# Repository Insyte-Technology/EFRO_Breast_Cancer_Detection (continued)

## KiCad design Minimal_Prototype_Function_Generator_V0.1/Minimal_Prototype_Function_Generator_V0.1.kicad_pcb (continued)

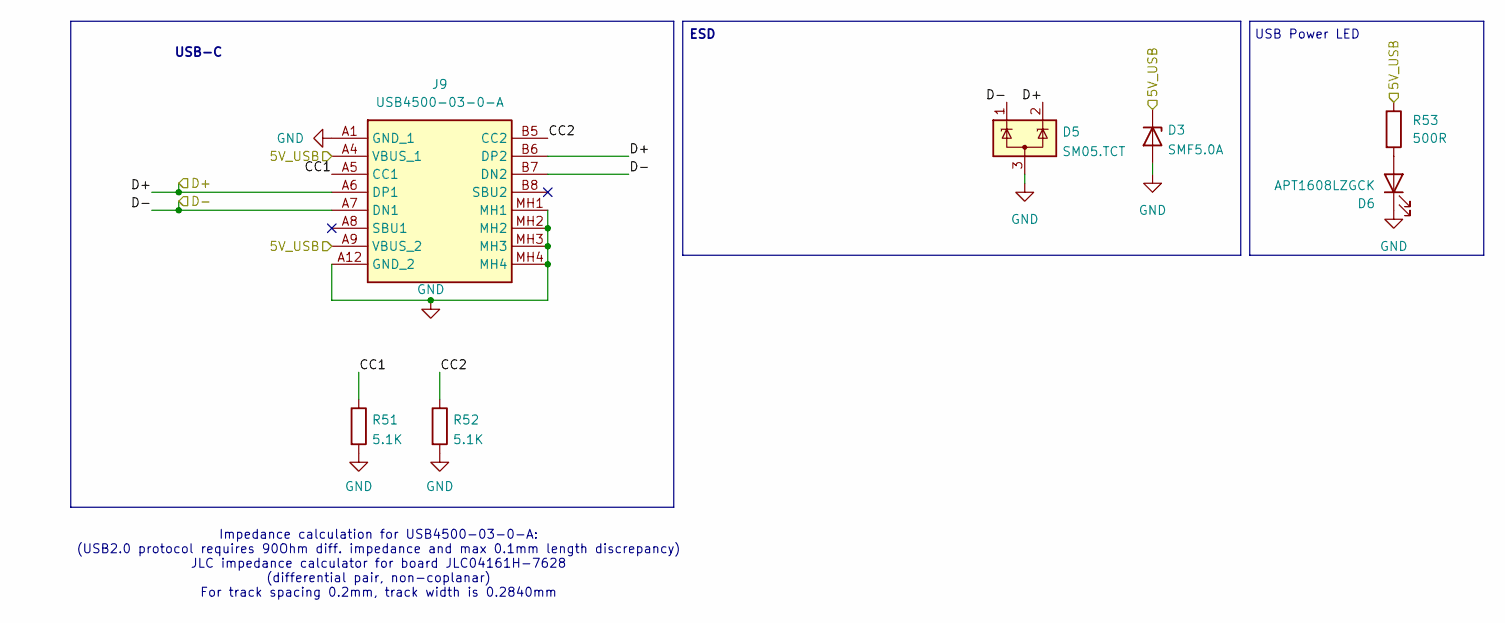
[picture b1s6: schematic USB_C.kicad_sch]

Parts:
D3: SMF5.0A; SODFL3618X110N; Manufacturer_Part_Number SMF5.0A; LCSC Part # C193402
D5: SM05.TCT; SOT95P237X125-3N; Manufacturer_Part_Number SM05.TCT; LCSC Part # C2687125
D6: APT1608LZGCK; CSL1901MW1; Manufacturer_Part_Number APT1608LZGCK
J9: USB4500-03-0-A; USB4500030A; Mouser Part Number 640-USB4500030A
R51, R52: 5.1K; R_0603; Manufacturer_Part_Number RT0603FRD075K1L; LCSC Part # C23186
R53: 500R; R_0603; Manufacturer_Part_Number RC0603FR-1325K5L

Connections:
/Power/5V: D3.1 (K), J9.A4 (VBUS_1), J9.A9 (VBUS_2), R53.1; also elsewhere on the board
/USB_C/CC1: J9.A5 (CC1), R51.1
/USB_C/CC2: J9.B5 (CC2), R52.1
/USB_C/D+: D5.2 (K), J9.A6 (DP1), J9.B6 (DP2); also elsewhere on the board
/USB_C/D-: D5.1 (K), J9.A7 (DN1), J9.B7 (DN2); also elsewhere on the board
GND: D3.2 (A), D5.3 (A), D6.1 (K), J9.A1 (GND_1), J9.A12 (GND_2), J9.MH1, J9.MH2, J9.MH3, J9.MH4, R51.2, R52.2; also elsewhere on the board
unnamed: D6.2 (A), R53.2

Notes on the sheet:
Impedance calculation for USB4500-03-0-A: (USB2.0 protocol requires 90Ohm diff. impedance and max 0.1mm length discrepancy) JLC impedance calculator for board JLC04161H-7628 (differential pair, non-coplanar) For track spacing 0.2mm, track width is 0.2840mm
ESD
USB-C
USB Power LED

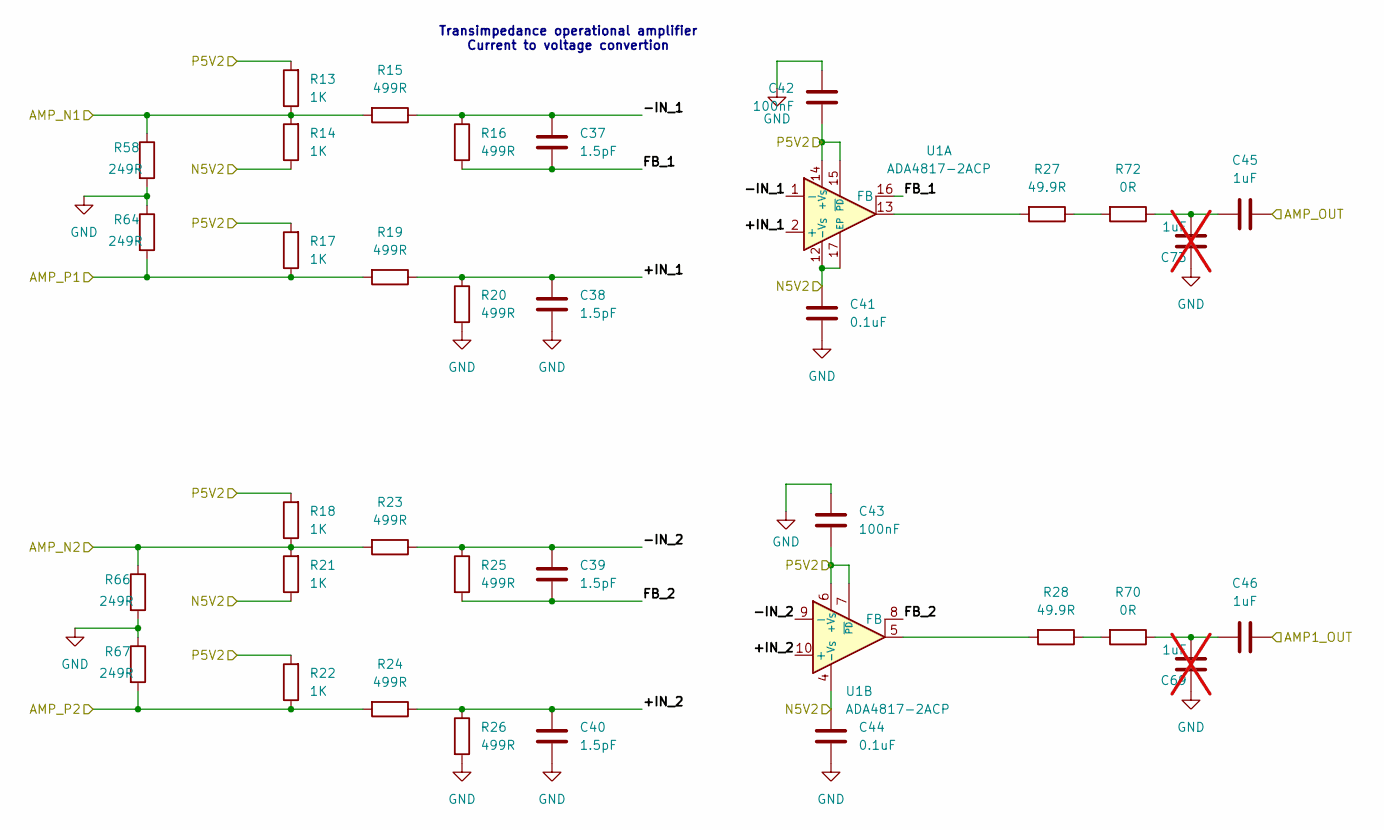
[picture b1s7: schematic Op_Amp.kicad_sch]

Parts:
C37, C38, C39, C40: 1.5pF; C_0603
C41, C44: 0.1uF; C_0603
C42, C43: 100nF; C_0603
C45, C46: 1uF; C_0603
C69, C73: 1uF; C_0603; not fitted
R13, R14, R17, R18, R21, R22: 1K; R_0603
R15, R16, R19, R20, R23, R24, R25, R26: 499R; R_0603
R27, R28: 49.9R; R_0603
R58, R64, R66, R67: 249R; R_0603
R70, R72: 0R; R_0603
U1: ADA4817-2ACP; Analog_LFCSP-16-1EP_4x4mm_P0.65mm_EP2.35x2.35mm

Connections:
/Function Generator/I_Out_N1: R13.1, R14.2, R15.2, R58.1; also elsewhere on the board
/Function Generator/I_Out_N2: R18.1, R21.2, R23.2, R66.1; also elsewhere on the board
/Function Generator/I_Out_P1: R17.1, R19.2, R64.2; also elsewhere on the board
/Function Generator/I_Out_P2: R22.1, R24.2, R67.2; also elsewhere on the board
/Output_Stage/N5V2: C41.1, C44.1, R14.1, R21.1, U1.4 (-V_{S}), U1.12 (-V_{S}), U1.17 (EP); also elsewhere on the board
/Output_Stage/Op_Amp_1/+IN_1: C38.1, R19.1, R20.1, U1.2 (+)
/Output_Stage/Op_Amp_1/+IN_2: C40.1, R24.1, R26.1, U1.10 (+)
/Output_Stage/Op_Amp_1/-IN_1: C37.1, R15.1, R16.1, U1.1 (-)
/Output_Stage/Op_Amp_1/-IN_2: C39.1, R23.1, R25.1, U1.9 (-)
/Output_Stage/Op_Amp_1/AMP1_OUT: C46.2; also elsewhere on the board
/Output_Stage/Op_Amp_1/AMP_OUT: C45.2; also elsewhere on the board
/Output_Stage/Op_Amp_1/FB_1: C37.2, R16.2, U1.16 (FB)
/Output_Stage/Op_Amp_1/FB_2: C39.2, R25.2, U1.8 (FB)
/Output_Stage/P5V2: C42.2, C43.2, R13.2, R17.2, R18.2, R22.2, U1.6 (+V_{S}), U1.7 (~PD), U1.14 (+V_{S}), U1.15 (~PD); also elsewhere on the board
GND: C38.2, C40.2, C41.2, C42.1, C43.1, C44.2, C69.2, C73.2, R20.2, R26.2, R58.2, R64.1, R66.2, R67.1; also elsewhere on the board
unnamed: C45.1, C73.1, R72.1
unnamed: C46.1, C69.1, R70.1
unnamed: R27.1, R72.2
unnamed: R27.2, U1.13
unnamed: R28.1, R70.2
unnamed: R28.2, U1.5

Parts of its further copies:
C47, C48, C49, C50: 1.5pF; C_0603
C51, C53: 100nF; C_0603
C52, C54: 0.1uF; C_0603
C55, C56: 1uF; C_0603
C72, C74: 1uF; C_0603; not fitted
R29, R30, R31, R32, R33, R34: 1K; R_0603
R35, R36, R37, R38, R39, R40, R41, R42: 499R; R_0603
R43, R44: 49.9R; R_0603
R63, R65, R68, R69: 249R; R_0603
R71, R73: 0R; R_0603
U3: ADA4817-2ACP; Analog_LFCSP-16-1EP_4x4mm_P0.65mm_EP2.35x2.35mm

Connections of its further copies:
/Function Generator/I_Out_N3: R29.1, R30.2, R35.2, R63.1; also elsewhere on the board
/Function Generator/I_Out_N4: R32.1, R33.2, R37.2, R68.1; also elsewhere on the board
/Function Generator/I_Out_P3: R31.1, R36.2, R65.2; also elsewhere on the board
/Function Generator/I_Out_P4: R34.1, R38.2, R69.2; also elsewhere on the board
/Output_Stage/N5V2: C52.1, C54.1, R30.1, R33.1, U3.4 (-V_{S}), U3.12 (-V_{S}), U3.17 (EP); also elsewhere on the board
/Output_Stage/Op_Amp_2/+IN_1: C48.1, R36.1, R40.1, U3.2 (+)
/Output_Stage/Op_Amp_2/+IN_2: C50.1, R38.1, R42.1, U3.10 (+)
/Output_Stage/Op_Amp_2/-IN_1: C47.1, R35.1, R39.1, U3.1 (-)
/Output_Stage/Op_Amp_2/-IN_2: C49.1, R37.1, R41.1, U3.9 (-)
/Output_Stage/Op_Amp_2/AMP1_OUT: C56.2; also elsewhere on the board
/Output_Stage/Op_Amp_2/AMP_OUT: C55.2; also elsewhere on the board
/Output_Stage/Op_Amp_2/FB_1: C47.2, R39.2, U3.16 (FB)
/Output_Stage/Op_Amp_2/FB_2: C49.2, R41.2, U3.8 (FB)
/Output_Stage/P5V2: C51.2, C53.2, R29.2, R31.2, R32.2, R34.2, U3.6 (+V_{S}), U3.7 (~PD), U3.14 (+V_{S}), U3.15 (~PD); also elsewhere on the board
GND: C48.2, C50.2, C51.1, C52.2, C53.1, C54.2, C72.2, C74.2, R40.2, R42.2, R63.2, R65.1, R68.2, R69.1; also elsewhere on the board
unnamed: C55.1, C74.1, R73.1
unnamed: C56.1, C72.1, R71.1
unnamed: R43.1, R73.2
unnamed: R43.2, U3.13
unnamed: R44.1, R71.2
unnamed: R44.2, U3.5

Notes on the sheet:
Transimpedance operational amplifier Current to voltage convertion

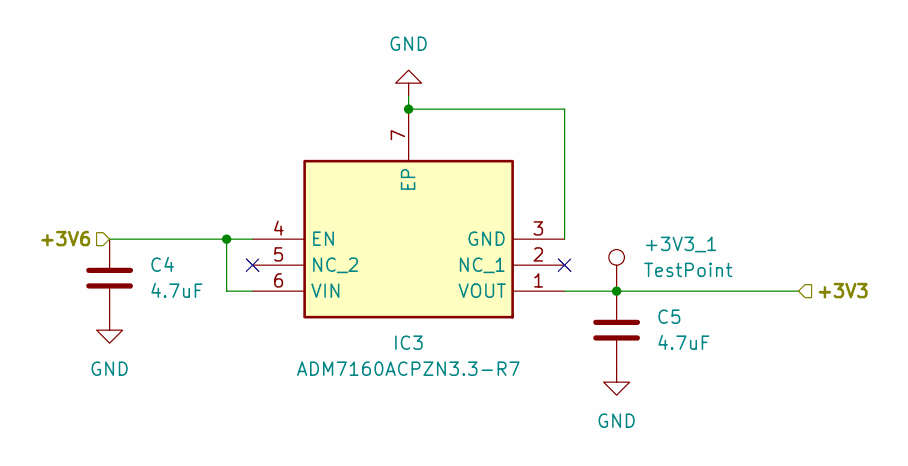
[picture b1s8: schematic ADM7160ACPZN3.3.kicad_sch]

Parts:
+3V3_1: TestPoint; Testpoint_hole
C4, C5: 4.7uF; C_0603
IC3: ADM7160ACPZN3.3-R7; SON65P200X200X65-7N-D; Mouser Part Number 584-DM7160ACPZN3.3R7

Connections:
/Power/ADM7160ACPZN3.3_1/+3V3: +3V3_1.1 (1_1), C5.1, IC3.1 (VOUT); also elsewhere on the board
/Power/ADM7160ACPZN3.3_1/+3V6: C4.1, IC3.4 (EN), IC3.6 (VIN); also elsewhere on the board
GND: C4.2, C5.2, IC3.3 (GND), IC3.7 (EP); also elsewhere on the board

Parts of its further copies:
+3V3_3, +3V3_4, +3V3_5: TestPoint; Testpoint_hole
C33, C34, C35, C36, C67, C68: 4.7uF; C_0603
IC6, IC7, IC8: ADM7160ACPZN3.3-R7; SON65P200X200X65-7N-D; Mouser Part Number 584-DM7160ACPZN3.3R7

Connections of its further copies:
/Function Generator/AVDD: +3V3_3.1 (1_1), C34.1, IC6.1 (VOUT); also elsewhere on the board
/Function Generator/CVDDX: +3V3_4.1 (1_1), C36.1, IC7.1 (VOUT); also elsewhere on the board
/Power/ADM7160ACPZN3.3_1/+3V6: C33.1, C35.1, C67.1, IC6.4 (EN), IC6.6 (VIN), IC7.4 (EN), IC7.6 (VIN), IC8.4 (EN), IC8.6 (VIN); also elsewhere on the board
/Power/VDD_STM32: +3V3_5.1 (1_1), C68.1, IC8.1 (VOUT); also elsewhere on the board
GND: C33.2, C34.2, C35.2, C36.2, C67.2, C68.2, IC6.3 (GND), IC6.7 (EP), IC7.3 (GND), IC7.7 (EP), IC8.3 (GND), IC8.7 (EP); also elsewhere on the board

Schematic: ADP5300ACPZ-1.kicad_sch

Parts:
+3V6_1, +5V_1: TestPoint; Testpoint_hole
C2, C3: 10uF; C_0603
D1: LED GREEN; CSL1901MW1
IC2: ADP5300ACPZ-1-R7; SON50P300X300X85-11N-D; Mouser Part Number 584-ADP5300ACPZ-1-R7
L1: MLP2016V2R2MT0S1; INDC2016X100N; Mouser Part Number 810-MLP2016H2R2MT0S1
R1: 499K; R_0603
R2: 5K; R_0603
R3: 0R; R_0603

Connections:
/Power/5V: +5V_1.1 (1_1), C2.1, IC2.1 (EN), IC2.3 (SYNC/MODE), IC2.10 (PVIN); also elsewhere on the board
/Power/ADM7160ACPZN3.3_1/+3V6: +3V6_1.1 (1_1), C3.1, IC2.5 (FB), L1.2, R2.1; also elsewhere on the board
GND: C2.2, C3.2, D1.1 (K), IC2.2 (STOP), IC2.7 (AGND), IC2.8 (PGND), IC2.11 (EP), R1.2; also elsewhere on the board
unnamed: D1.2 (A), IC2.6 (VOUTOK), R3.2
unnamed: IC2.9 (SW), L1.1
unnamed: IC2.4 (VID), R1.1
unnamed: R2.2, R3.1

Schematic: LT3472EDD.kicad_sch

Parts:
C23, C28, C30: 2.2uF; C_0603
C24: 1uF; C_0402
C25, C26: 0.1uF; C_0603
C27: 4.7pF; C_0603
C29: 10pF; C_0603
IC4: LT3472EDD#PBF; SON50P300X300X80-11N-D; Mouser Part Number 584-LT3472EDD#PBF
L2: 22uH; LQH32CH100K53L; Mouser Part Number 81-LQH32CN220K53L
L3, L4: 47uH; LQH32CH100K53L; Mouser Part Number 81-LQH32CN470K53L
N5V2_TP1: TestPoint; Testpoint_hole
P5V2_TP1: TestPoint; Testpoint_hole
R11: 158K; R_0603
R12: 210K; R_0603
R54, R55: 0R; R_0603

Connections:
/Output_Stage/N5V2: N5V2_TP1.1 (1_1), R55.2; also elsewhere on the board
/Output_Stage/P5V2: P5V2_TP1.1 (1_1), R54.2; also elsewhere on the board
/Power/5V: C23.1, IC4.2 (VIN), IC4.3 (~SHDN), L2.1, L2.3, L3.2, L3.4; also elsewhere on the board
/Power/LT3472EDD/N5V2_VN: C29.2, C30.1, L4.1, L4.3, R12.2, R55.1
/Power/LT3472EDD/P5V2_VP: C27.2, C28.1, IC4.10 (VPOS), R11.2, R54.1
GND: C23.2, C25.2, C26.2, C28.2, C30.2, IC4.11 (EP); also elsewhere on the board
unnamed: C24.2, IC4.5 (DN), L4.2, L4.4
unnamed: C29.1, IC4.6 (FBN), R12.1
unnamed: C27.1, IC4.8 (FBP), R11.1
unnamed: C26.1, IC4.7 (SSN)
unnamed: C25.1, IC4.9 (SSP)
unnamed: C24.1, IC4.4 (SWN), L3.1, L3.3
unnamed: IC4.1 (SWP), L2.2, L2.4

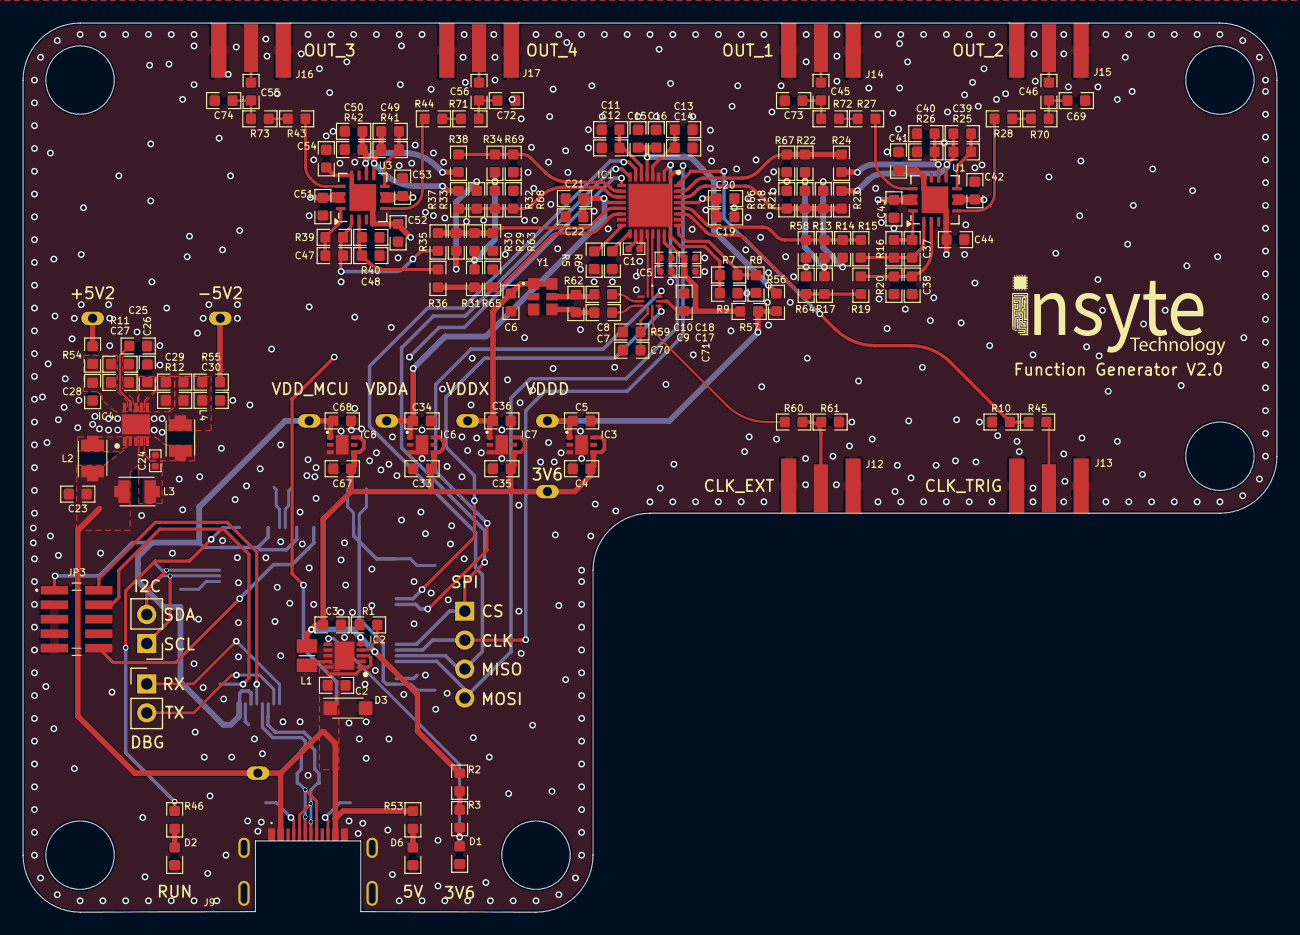
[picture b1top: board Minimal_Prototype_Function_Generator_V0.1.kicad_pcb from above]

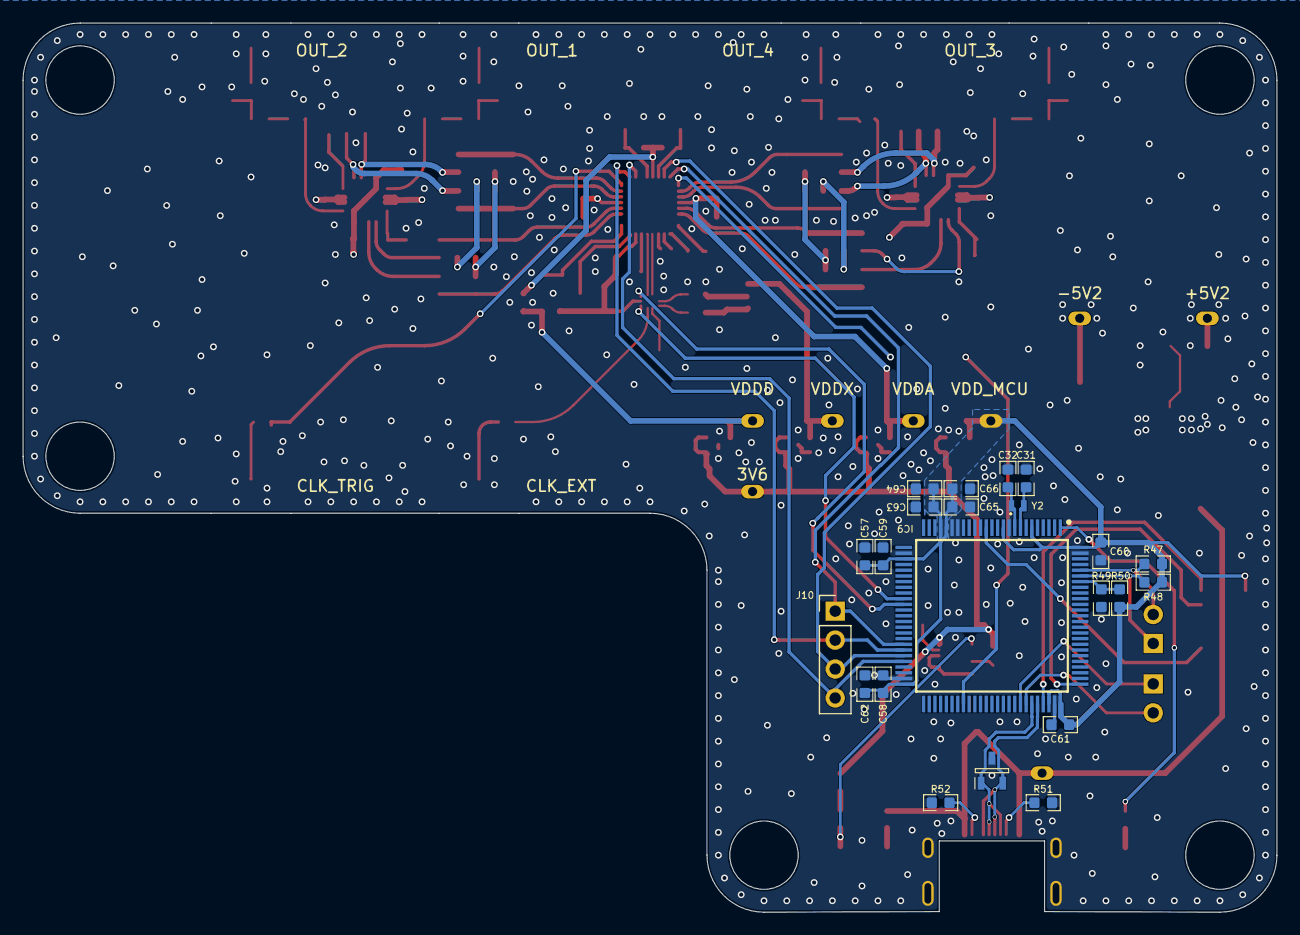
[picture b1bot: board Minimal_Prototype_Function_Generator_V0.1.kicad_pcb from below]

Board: 4 copper layers, 110.0 x 78.0 mm, 187 parts (29 on the bottom side), 103 nets.

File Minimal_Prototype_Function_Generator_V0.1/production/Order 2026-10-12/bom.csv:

Designator,Footprint,Quantity,Value,LCSC Part #
"+3V3_1, +3V3_3, +3V3_4, +3V3_5, +3V6_1, +5V_1, N5V2_TP1, P5V2_TP1",Testpoint_hole,8,TestPoint,
"C1, C17, C9",C_0402,3,0.1uF,
"C10, C18",C_0402,2,100pF,
"C11, C13, C15, C19, C21, C25, C26, C41, C44, C52, C54",C_0603,11,0.1uF,
"C12, C16, C20, C22",C_0603,4,100pF,
C14,C_0603,1,0.01uF,
"C2, C3",C_0603,2,10uF,
"C23, C28, C30",C_0603,3,2.2uF,
C24,C_0402,1,1uF,
C27,C_0603,1,4.7pF,
C29,C_0603,1,10pF,
"C31, C32",C_0603,2,8pF C0G/NP0  >5%,C36508
"C33, C34, C35, C36, C4, C5, C67, C68",C_0603,8,4.7uF,
"C37, C38, C39, C40, C47, C48, C49, C50",C_0603,8,1.5pF,
"C42, C43, C51, C53, C6, C7, C70, C71, C8",C_0603,9,100nF,
"C45, C46, C55, C56",C_0603,4,1uF,
"C57, C58, C59, C60, C61, C65",C_0603,6,0.1uF, C14663
C62,C_0603,1,4.7uF, C19702
C63,C_0603,1,0.01uF,C1589
"C64, C66",C_0603,2,1uF, C15849
D1,CSL1901MW1,1,LED GREEN,
D2,CSL1901MW1,1,CSL1901MW1,
D3,SODFL3618X110N,1,SMF5.0A,C193402
D5,SOT95P237X125-3N,1,SM05.TCT,C2687125
D6,CSL1901MW1,1,APT1608LZGCK,
IC1,QFN50P500X500X80-33N-D,1,AD9106BCPZ,
IC2,SON50P300X300X85-11N-D,1,ADP5300ACPZ-1-R7,
"IC3, IC6, IC7, IC8",SON65P200X200X65-7N-D,4,ADM7160ACPZN3.3-R7,
IC4,SON50P300X300X80-11N-D,1,LT3472EDD#PBF,
IC5,TMUXHS221FRSWR,1,TMUXHS221FRSWR,
IC9,QFP50P1600X1600X160-100N,1,STM32L476VGT6,
"J12, J13, J14, J15, J16, J17",142-0701-851,6,SMA-J-P-H-ST-EM1,
J9,USB4500030A,1,USB4500-03-0-A,
JP3,2002112100010C4LF,1,20021121-00010C4LF,C150517
L1,INDC2016X100N,1,MLP2016V2R2MT0S1,
L2,LQH32CH100K53L,1,22uH,
"L3, L4",LQH32CH100K53L,2,47uH,
R1,R_0603,1,499K,
R10,R_0603,1,9.1K,
R11,R_0603,1,158K,
R12,R_0603,1,210K,
"R13, R14, R17, R18, R21, R22, R29, R30, R31, R32, R33, R34",R_0603,12,1K,
"R15, R16, R19, R20, R23, R24, R25, R26, R35, R36, R37, R38, R39, R40, R41, R42",R_0603,16,499R,
R2,R_0603,1,5K,
"R27, R28, R43, R44",R_0603,4,49.9R,
"R3, R54, R55, R56, R57, R7, R70, R71, R72, R73",R_0603,10,0R,
R45,R_0603,1,4.7K,
R46,R_0603,1,750, C23241
"R47, R48",R_0603,2,4K7, C23162
R49,R_0603,1,10K,
"R5, R6, R8, R9",R_0603,4,8.06K,
"R51, R52",R_0603,2,5.1K,C23186
R53,R_0603,1,500R,
"R58, R63, R64, R65, R66, R67, R68, R69",R_0603,8,249R,
R59,R_0603,1,39K,
"R60, R62",R_0603,2,100R,
R61,R_0603,1,50R,
"U1, U3",Analog_LFCSP-16-1EP_4x4mm_P0.65mm_EP2.35x2.35mm,2,ADA4817-2ACP,
Y1,AX3_3.2x2.5,1,AX3DCF1-156.2500T,
Y2,ECS327516TR,1,ECS-.327-7-16-C-TR,

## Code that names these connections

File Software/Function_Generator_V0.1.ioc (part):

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Mcu.Name=STM32L476V(C-E-G)Tx
Mcu.Package=LQFP100
Mcu.UserName=STM32L476VGTx
PA10.Mode=Asynchronous
PA10.Signal=USART1_RX
PA11.Mode=Device_Only
PA11.Signal=USB_OTG_FS_DM
PA12.Mode=Device_Only
PA12.Signal=USB_OTG_FS_DP
PA13\ (JTMS-SWDIO).Mode=Serial_Wire
PA13\ (JTMS-SWDIO).Signal=SYS_JTMS-SWDIO
PA14\ (JTCK-SWCLK).Mode=Serial_Wire
PA14\ (JTCK-SWCLK).Signal=SYS_JTCK-SWCLK
PA9.Mode=Asynchronous
PA9.Signal=USART1_TX
PB8.Mode=I2C
PB8.Signal=I2C1_SCL
PB9.Mode=I2C
PB9.Signal=I2C1_SDA
PC14-OSC32_IN\ (PC14).Signal=RCC_OSC32_IN
PC15-OSC32_OUT\ (PC15).Signal=RCC_OSC32_OUT
PD11.GPIOParameters=GPIO_Label
PD11.GPIO_Label=FUNC_RESET
PD11.Signal=GPIO_Output
PE12.GPIOParameters=GPIO_Label
PE12.GPIO_Label=SPI_CS
PE12.Signal=GPIO_Output
PE13.Mode=Full_Duplex_Master
PE13.Signal=SPI1_SCK
PE14.Mode=Full_Duplex_Master
PE14.Signal=SPI1_MISO
PE15.Mode=Full_Duplex_Master
PE15.Signal=SPI1_MOSI
PE2.GPIOParameters=GPIO_Label
PE2.GPIO_Label=LED
PE2.Signal=GPIO_Output
RCC.HSE_VALUE=8000000
RCC.SYSCLKFreq_VALUE=80000000
RCC.SYSCLKSource=RCC_SYSCLKSOURCE_PLLCLK
board=custom

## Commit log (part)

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2025-12-15 working software prototype. hardware still has a couple of issues
2026-03-20 added cli to the project
